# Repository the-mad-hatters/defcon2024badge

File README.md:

# defcon2024badge

See https://madhatters.lol for details

The Mad Hatter Auto Revelator badge and Madragrammaton SAO will be available at the Hacker Warehouse at DC32.

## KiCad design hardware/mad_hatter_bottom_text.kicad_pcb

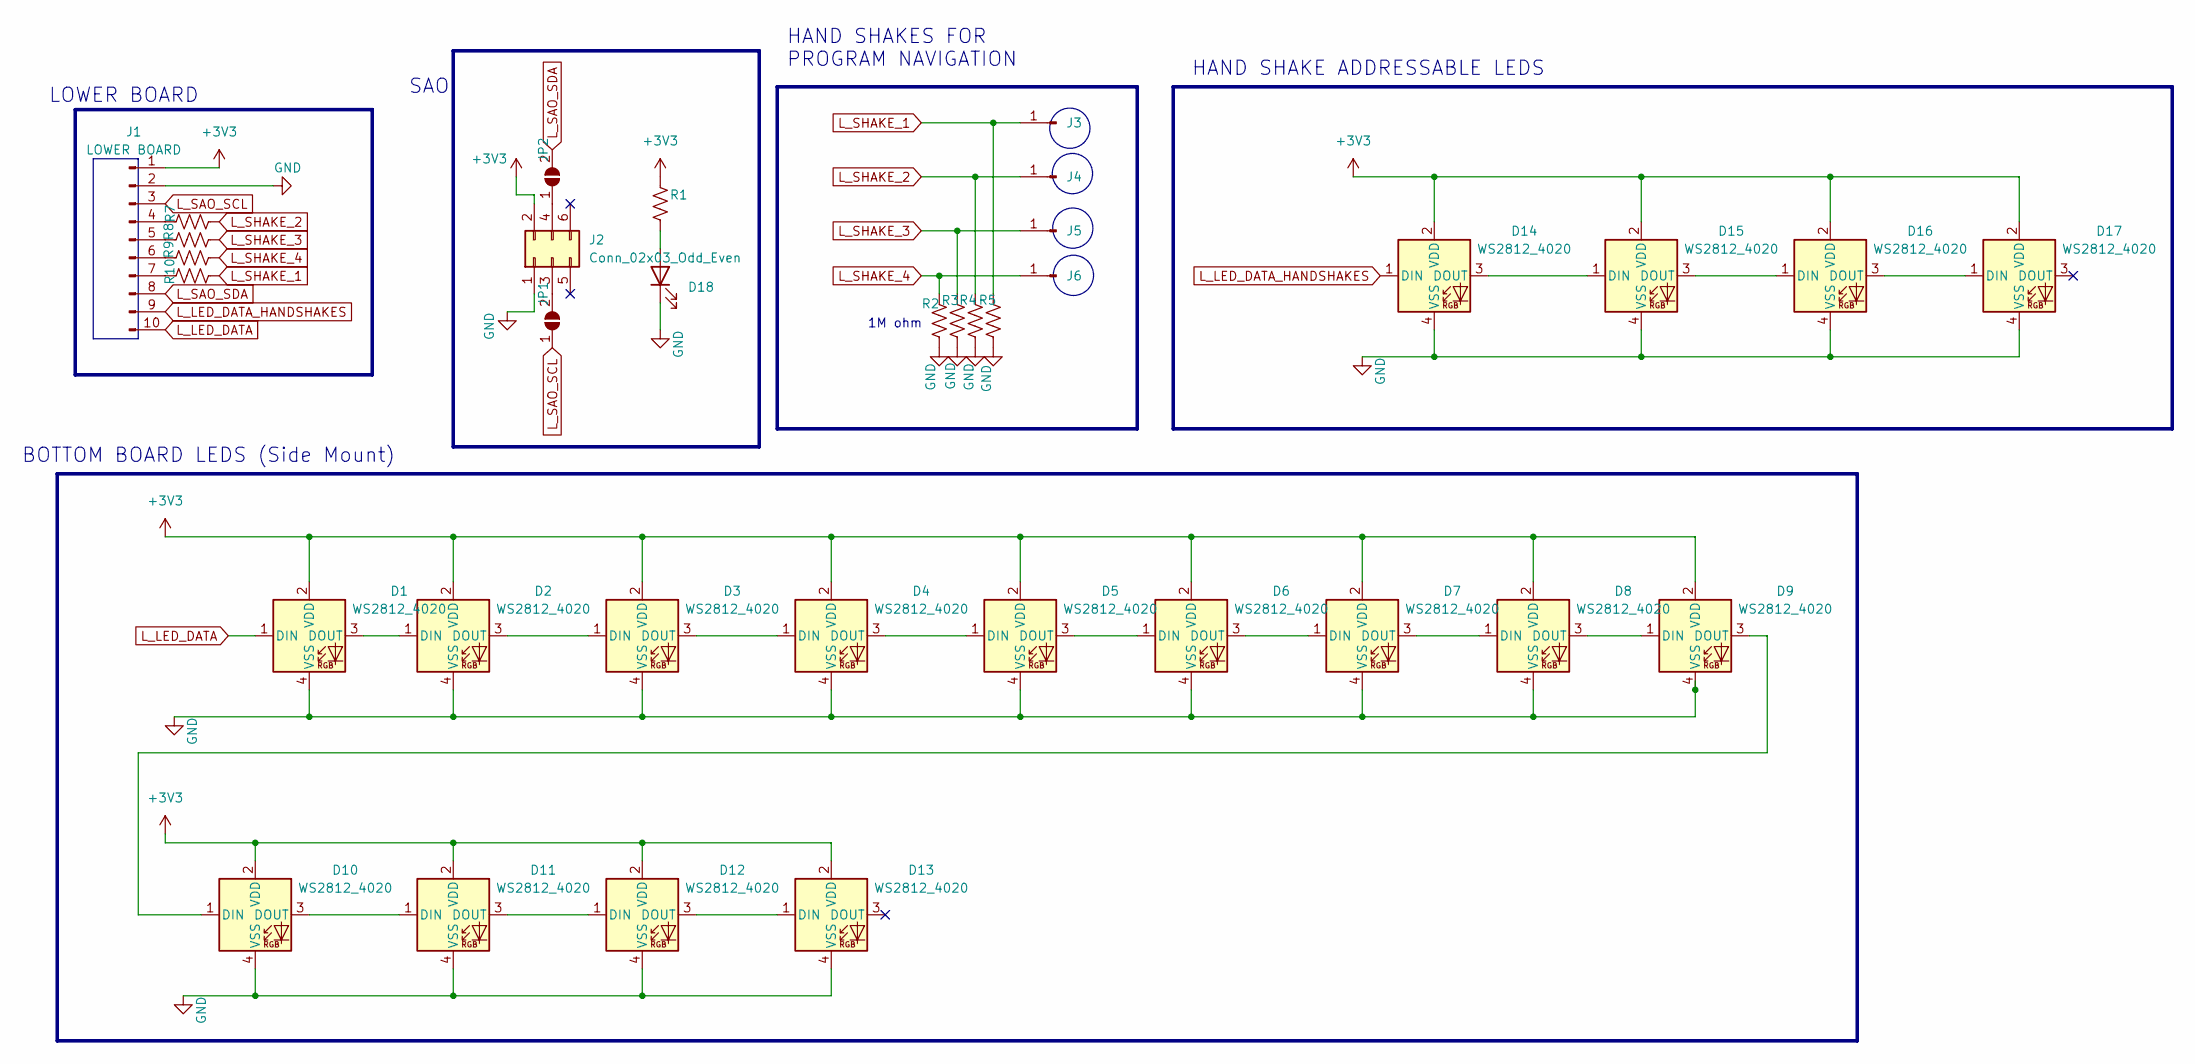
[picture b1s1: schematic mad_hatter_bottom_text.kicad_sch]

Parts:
D1, D2, D3, D4, D5, D6, D7, D8, D9, D10, D11, D12, D13, D14, D15, D16, D17: WS2812_4020; sk6812-side-a
D18: LED; LED_1206_3216Metric_Pad1.42x1.75mm_HandSolder
J1: LOWER BOARD; mad_hatter_lower_board_connector
J2: Conn_02x03_Odd_Even; sao_footprint
J3, J4, J5, J6: Conn_01x01_Pin; mad_hatter_touch_button
JP1, JP2: SolderJumper_2_Open; SolderJumper-2_P1.3mm_Open_Pad1.0x1.5mm
R1, R2, R3, R4, R5, R7, R8, R9, R10: R_US; R_0603_1608Metric_Pad0.98x0.95mm_HandSolder

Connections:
+3V3: D1.2 (VDD), D2.2 (VDD), D3.2 (VDD), D4.2 (VDD), D5.2 (VDD), D6.2 (VDD), D7.2 (VDD), D8.2 (VDD), D9.2 (VDD), D10.2 (VDD), D11.2 (VDD), D12.2 (VDD), D13.2 (VDD), D14.2 (VDD), D15.2 (VDD), D16.2 (VDD), D17.2 (VDD), J1.1, J2.2, R1.1
GND: D1.4 (VSS), D2.4 (VSS), D3.4 (VSS), D4.4 (VSS), D5.4 (VSS), D6.4 (VSS), D7.4 (VSS), D8.4 (VSS), D9.4 (VSS), D10.4 (VSS), D11.4 (VSS), D12.4 (VSS), D13.4 (VSS), D14.4 (VSS), D15.4 (VSS), D16.4 (VSS), D17.4 (VSS), D18.1 (K), J1.2, J2.1, R2.2, R3.2, R4.2, R5.2
L_LED_DATA: D1.1 (DIN), J1.10
L_LED_DATA_HANDSHAKES: D14.1 (DIN), J1.9
L_SAO_SCL: J1.3, JP1.1 (A)
L_SAO_SDA: J1.8, JP2.2 (B)
L_SHAKE_1: J3.1, R5.1, R10.1
L_SHAKE_2: J4.1, R4.1, R7.1
L_SHAKE_3: J5.1, R3.1, R8.1
L_SHAKE_4: J6.1, R2.1, R9.1
unnamed: D1.3 (DOUT), D2.1 (DIN)
unnamed: D2.3 (DOUT), D3.1 (DIN)
unnamed: D3.3 (DOUT), D4.1 (DIN)
unnamed: D4.3 (DOUT), D5.1 (DIN)
unnamed: D5.3 (DOUT), D6.1 (DIN)
unnamed: D6.3 (DOUT), D7.1 (DIN)
unnamed: D7.3 (DOUT), D8.1 (DIN)
unnamed: D8.3 (DOUT), D9.1 (DIN)
unnamed: D9.3 (DOUT), D10.1 (DIN)
unnamed: D10.3 (DOUT), D11.1 (DIN)
unnamed: D11.3 (DOUT), D12.1 (DIN)
unnamed: D12.3 (DOUT), D13.1 (DIN)
unnamed: D14.3 (DOUT), D15.1 (DIN)
unnamed: D15.3 (DOUT), D16.1 (DIN)
unnamed: D16.3 (DOUT), D17.1 (DIN)
unnamed: D18.2 (A), R1.2
unnamed: J1.4, R7.2
unnamed: J1.5, R8.2
unnamed: J1.6, R9.2
unnamed: J1.7, R10.2
unnamed: J2.3, JP1.2 (B)
unnamed: J2.4, JP2.1 (A)

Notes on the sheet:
HAND SHAKES FOR PROGRAM NAVIGATION
LOWER BOARD
SAO
HAND SHAKE ADDRESSABLE LEDS
BOTTOM BOARD LEDS (Side Mount)
1M ohm

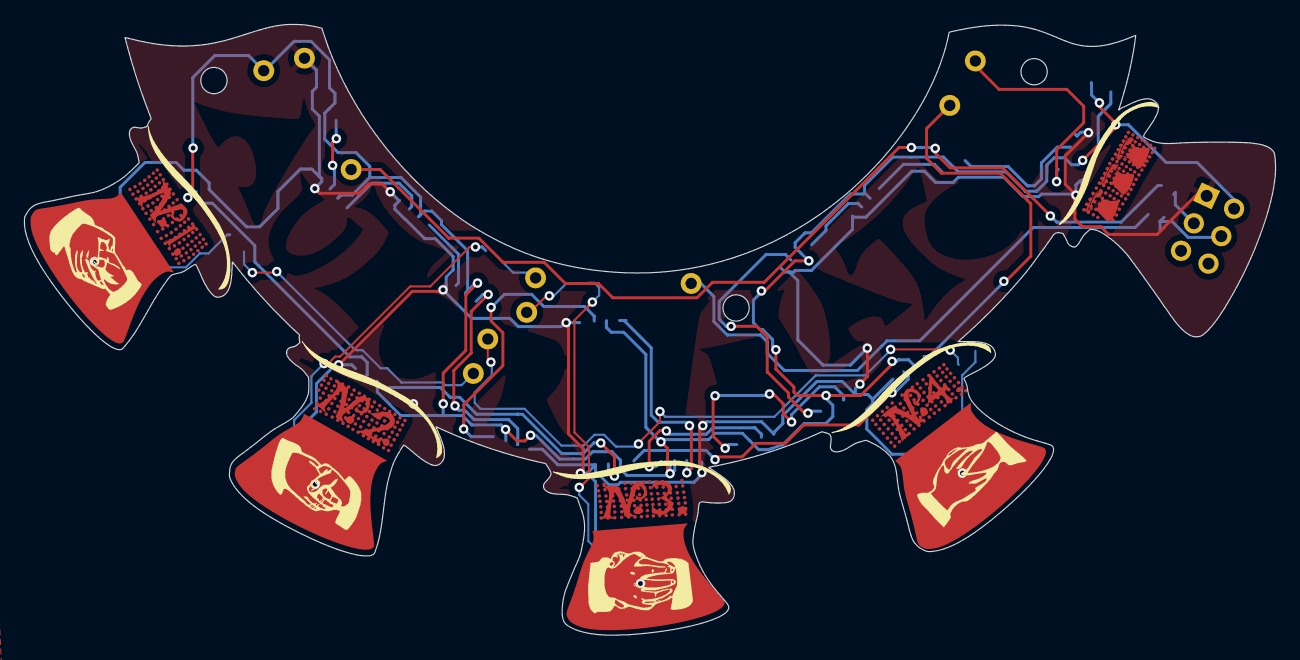
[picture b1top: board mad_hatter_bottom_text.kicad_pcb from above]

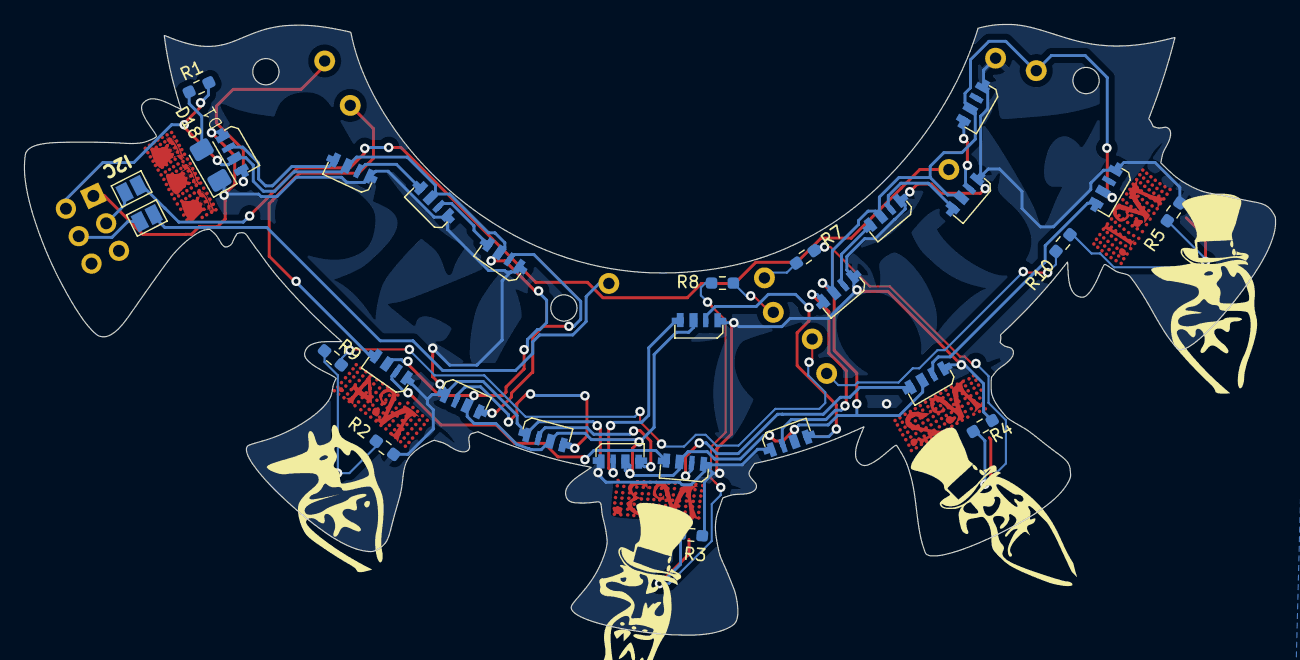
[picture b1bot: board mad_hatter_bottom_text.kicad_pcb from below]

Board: 2 copper layers, 104.9 x 51.2 mm, 35 parts (29 on the bottom side), 32 nets.

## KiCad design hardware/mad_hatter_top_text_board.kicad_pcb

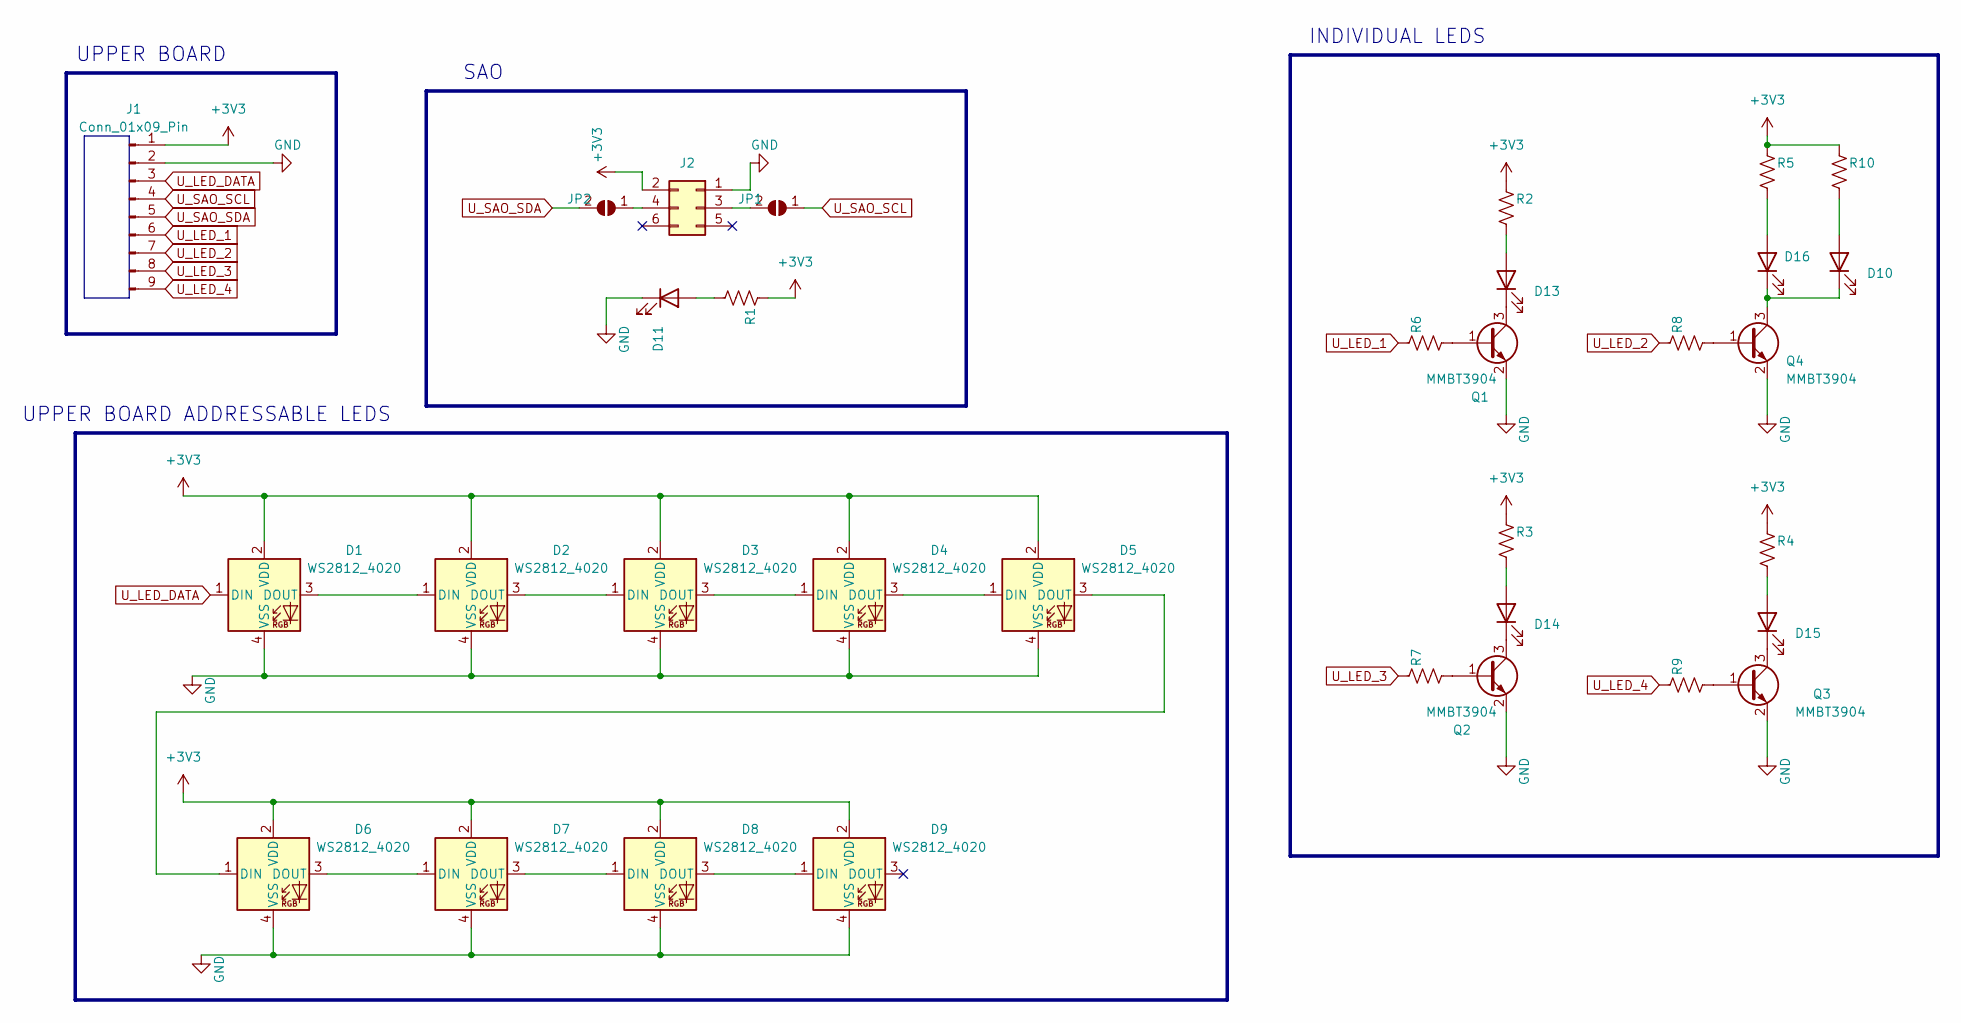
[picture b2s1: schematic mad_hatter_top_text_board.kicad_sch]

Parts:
D1, D2, D3, D4, D5, D6, D7, D8, D9: WS2812_4020; sk6812-side-a
D10: LED; LED_0805_2012Metric_Pad1.15x1.40mm_HandSolder
D11, D13, D14, D15, D16: LED; LED_1206_3216Metric_Pad1.42x1.75mm_HandSolder
J1: Conn_01x09_Pin; mad_hatter_upper_board_connector
J2: Conn_02x03_Odd_Even; sao_footprint
JP1, JP2: SolderJumper_2_Open; SolderJumper-2_P1.3mm_Open_Pad1.0x1.5mm
Q1, Q2, Q3, Q4: MMBT3904; SOT-23
R1, R2, R3, R4, R5, R6, R7, R8, R9, R10: R_US; R_0603_1608Metric_Pad0.98x0.95mm_HandSolder

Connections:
+3V3: D1.2 (VDD), D2.2 (VDD), D3.2 (VDD), D4.2 (VDD), D5.2 (VDD), D6.2 (VDD), D7.2 (VDD), D8.2 (VDD), D9.2 (VDD), J1.1, J2.2, R1.1, R2.1, R3.1, R4.1, R5.1, R10.1
GND: D1.4 (VSS), D2.4 (VSS), D3.4 (VSS), D4.4 (VSS), D5.4 (VSS), D6.4 (VSS), D7.4 (VSS), D8.4 (VSS), D9.4 (VSS), D11.1 (K), J1.2, J2.1, Q1.2 (E), Q2.2 (E), Q3.2 (E), Q4.2 (E)
unnamed: D1.3 (DOUT), D2.1 (DIN)
unnamed: D2.3 (DOUT), D3.1 (DIN)
unnamed: D3.3 (DOUT), D4.1 (DIN)
unnamed: D4.3 (DOUT), D5.1 (DIN)
unnamed: D5.3 (DOUT), D6.1 (DIN)
unnamed: D6.3 (DOUT), D7.1 (DIN)
unnamed: D7.3 (DOUT), D8.1 (DIN)
unnamed: D8.3 (DOUT), D9.1 (DIN)
unnamed: D10.2 (A), R10.2
unnamed: D10.1 (K), D16.1 (K), Q4.3 (C)
unnamed: D11.2 (A), R1.2
unnamed: D13.2 (A), R2.2
unnamed: D13.1 (K), Q1.3 (C)
unnamed: D14.2 (A), R3.2
unnamed: D14.1 (K), Q2.3 (C)
unnamed: D15.2 (A), R4.2
unnamed: D15.1 (K), Q3.3 (C)
unnamed: D16.2 (A), R5.2
unnamed: J2.3, JP1.2 (B)
unnamed: J2.4, JP2.1 (A)
unnamed: Q1.1 (B), R6.2
unnamed: Q2.1 (B), R7.2
unnamed: Q3.1 (B), R9.2
unnamed: Q4.1 (B), R8.2
U_LED_1: J1.6, R6.1
U_LED_2: J1.7, R8.1
U_LED_3: J1.8, R7.1
U_LED_4: J1.9, R9.1
U_LED_DATA: D1.1 (DIN), J1.3
U_SAO_SCL: J1.4, JP1.1 (A)
U_SAO_SDA: J1.5, JP2.2 (B)

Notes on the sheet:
UPPER BOARD
INDIVIDUAL LEDS
UPPER BOARD ADDRESSABLE LEDS
SAO

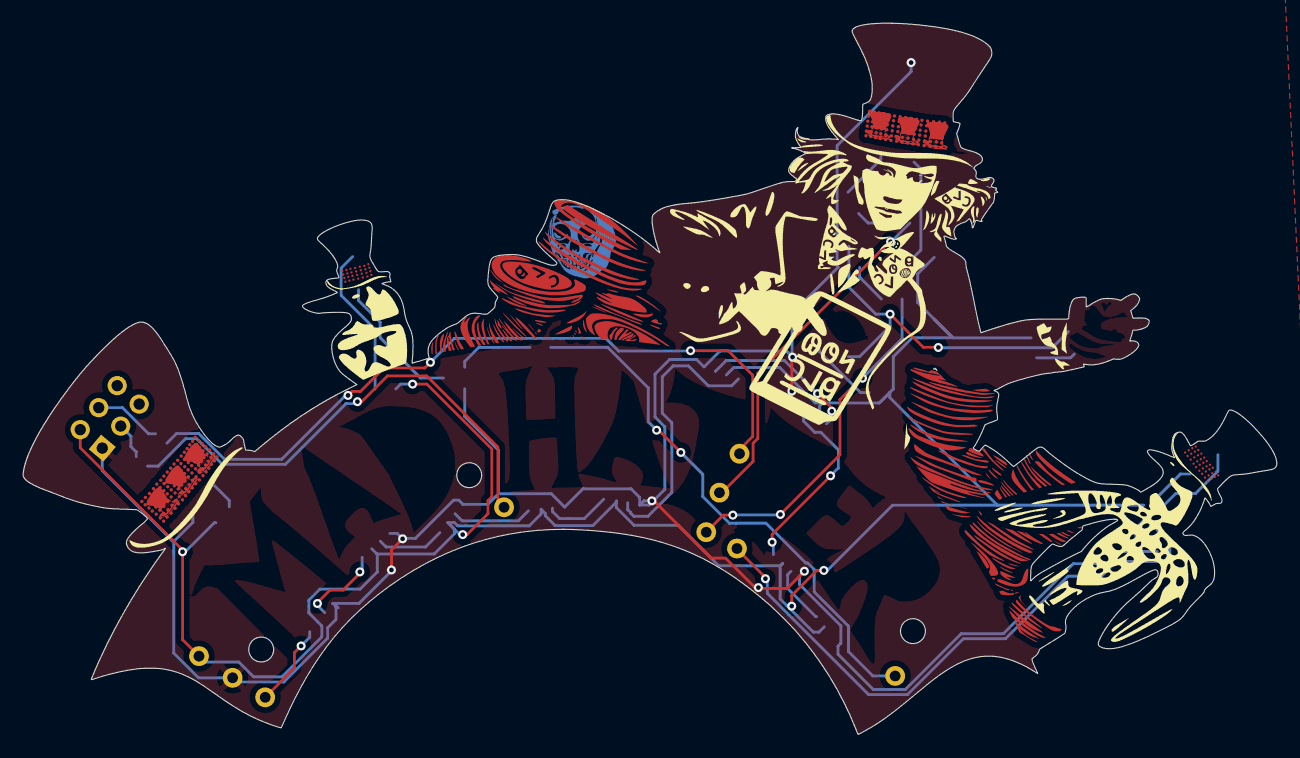
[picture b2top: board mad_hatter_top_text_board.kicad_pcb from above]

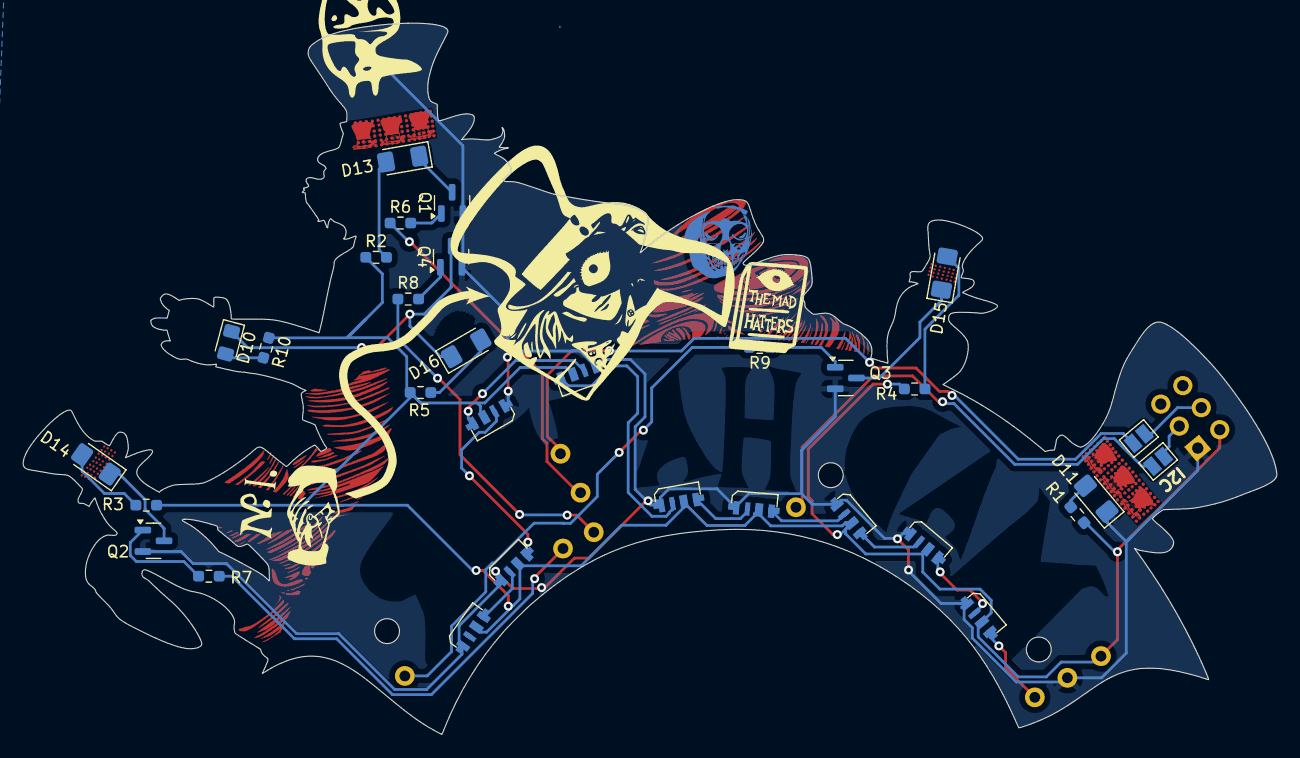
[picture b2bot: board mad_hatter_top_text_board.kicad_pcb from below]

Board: 2 copper layers, 110.8 x 62.9 mm, 33 parts (31 on the bottom side), 33 nets.

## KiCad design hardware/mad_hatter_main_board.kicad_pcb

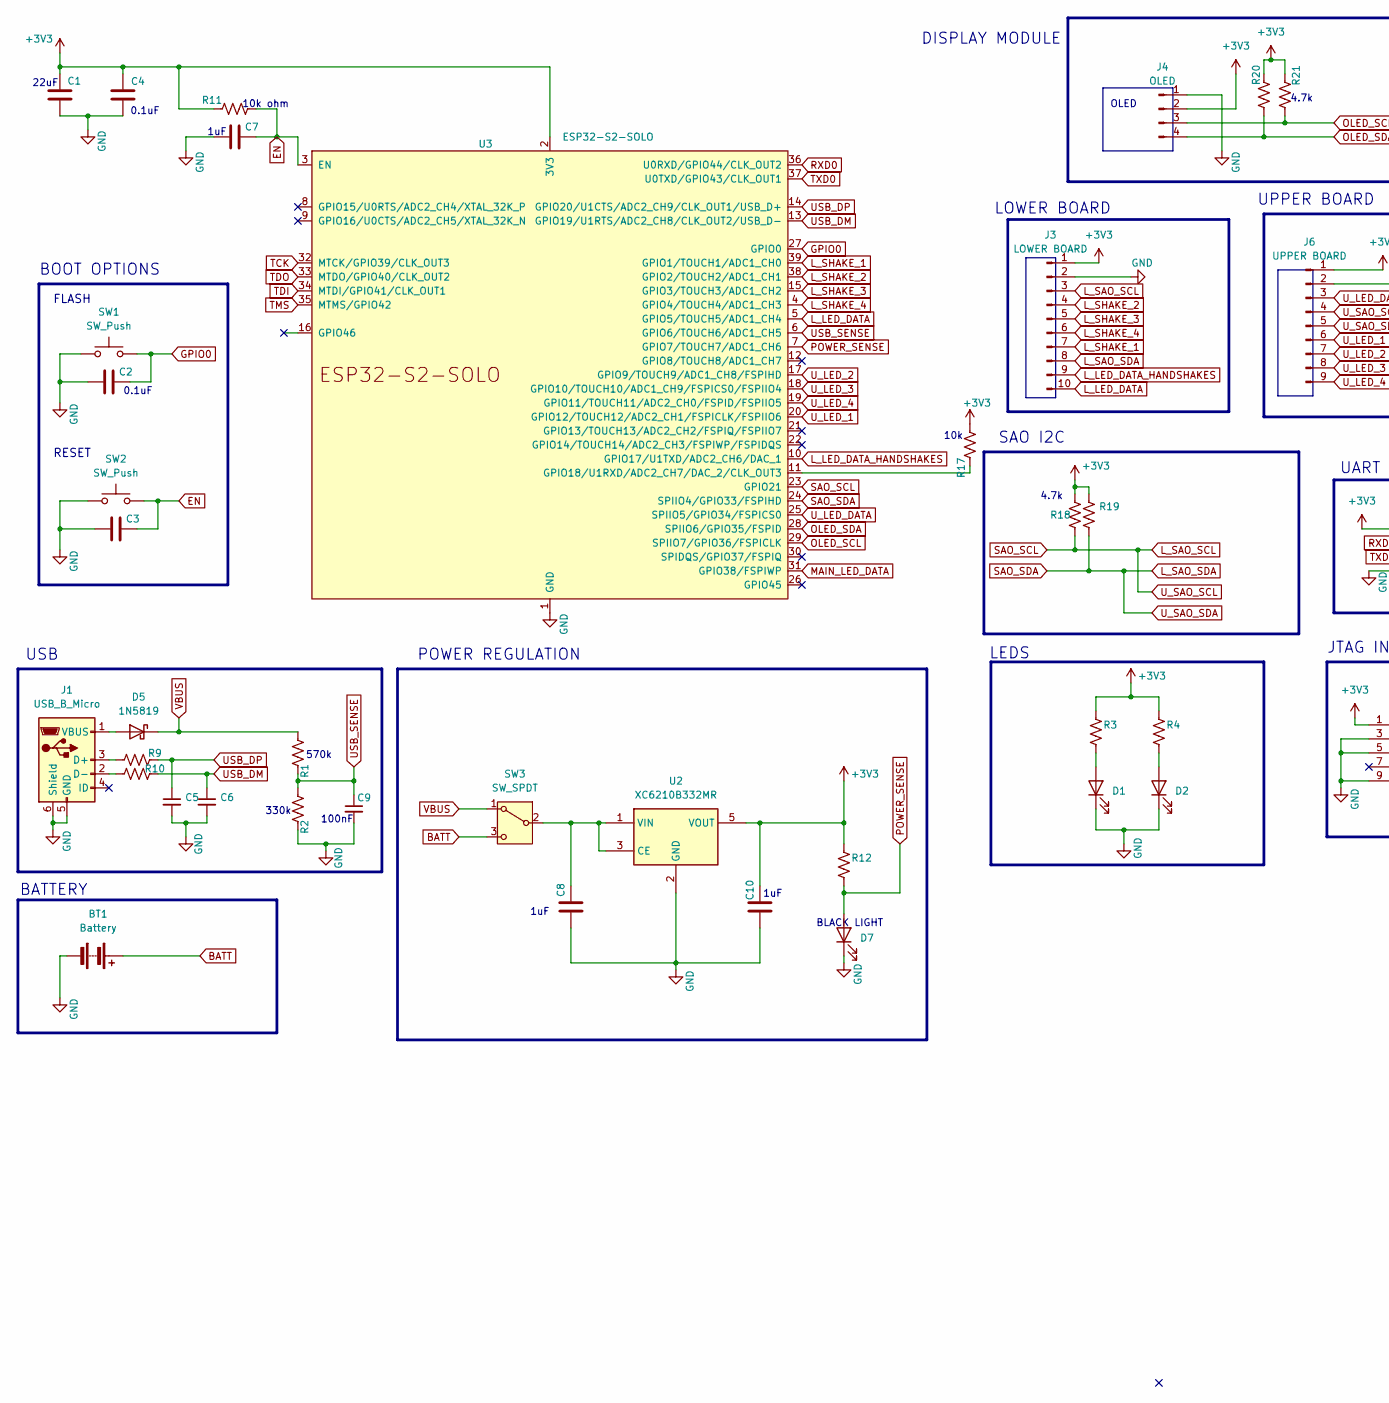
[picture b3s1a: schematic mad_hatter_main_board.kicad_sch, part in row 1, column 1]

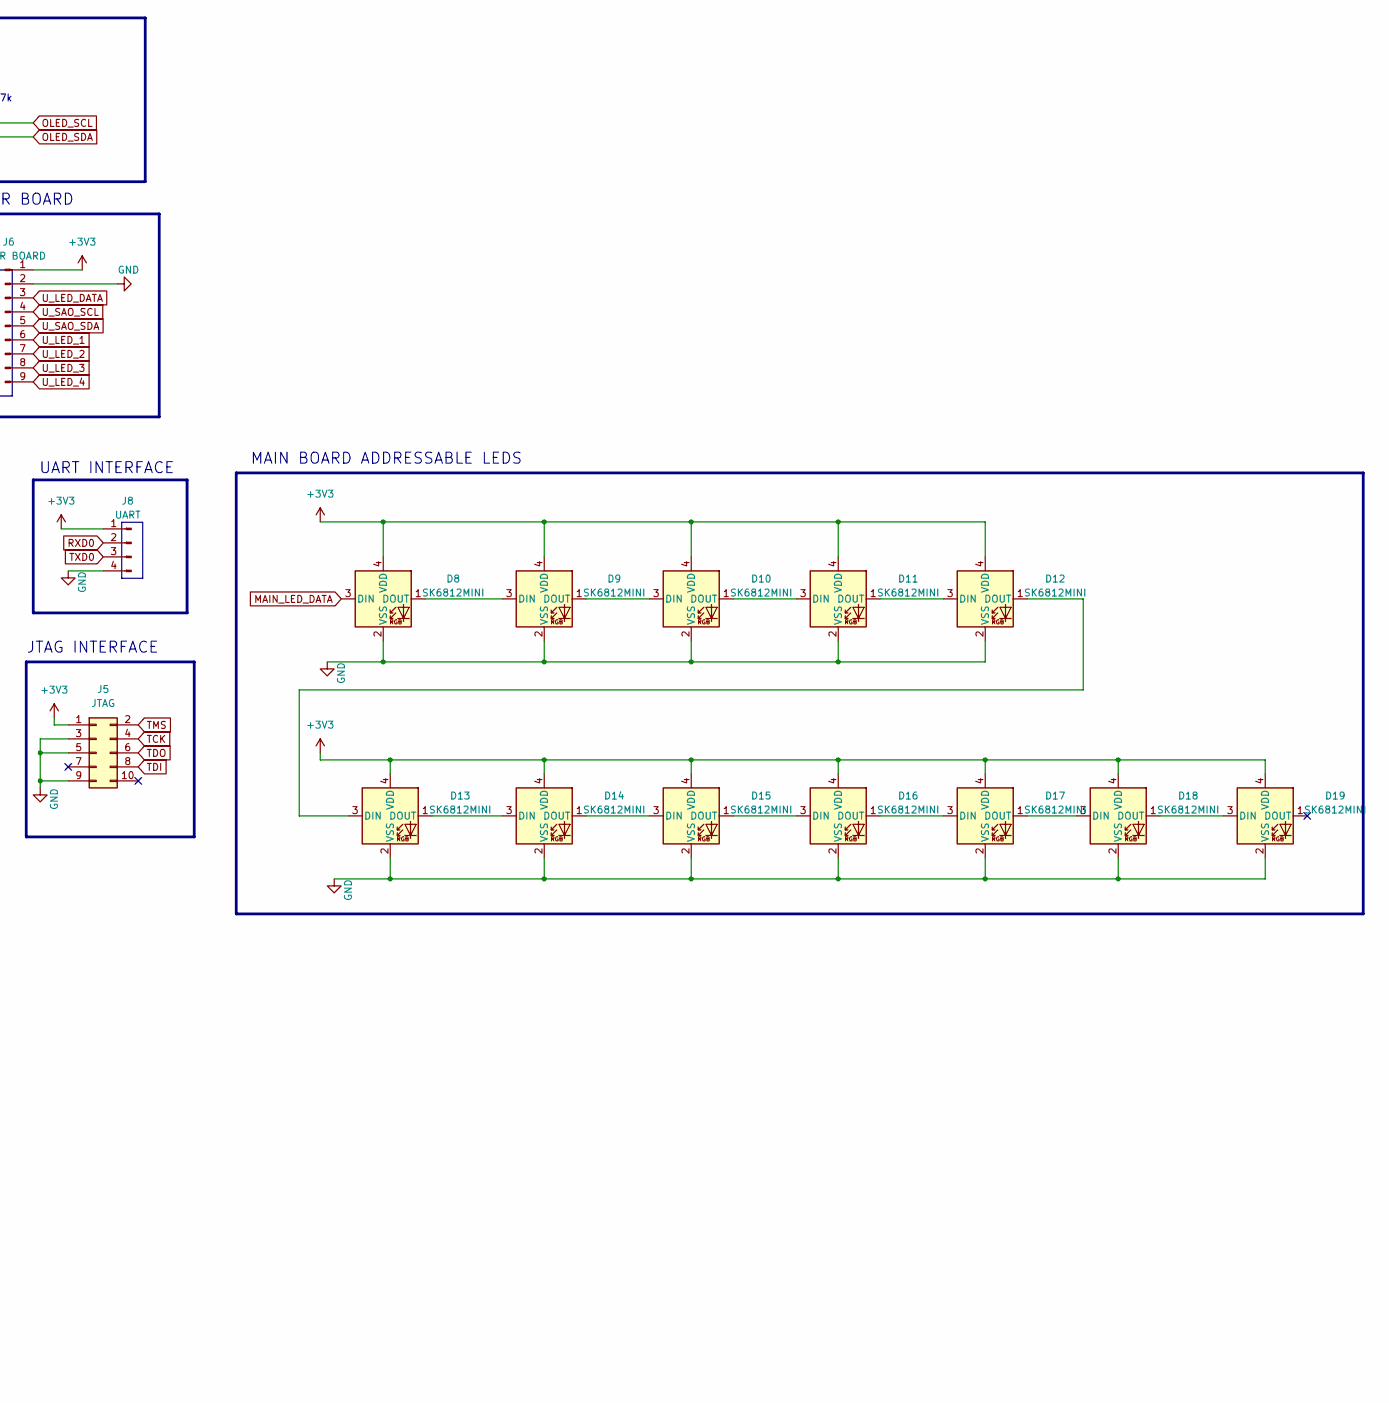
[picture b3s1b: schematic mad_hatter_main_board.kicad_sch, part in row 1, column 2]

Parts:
BT1: Battery; mad_hatter_3_AA_battery
C1: C; C_0805_2012Metric_Pad1.18x1.45mm_HandSolder
C2, C3, C4, C7, C8, C10: C; C_0603_1608Metric_Pad1.08x0.95mm_HandSolder
C5, C6, C9: 10uF; C_0603_1608Metric_Pad1.08x0.95mm_HandSolder
D1, D2, D7: LED; LED_1206_3216Metric_Pad1.42x1.75mm_HandSolder
D5: 1N5819; D_DO-41_SOD81_P10.16mm_Horizontal
D8, D9, D10, D11, D12, D13, D14, D15, D16, D17, D18, D19: SK6812MINI; mad_hatter_sk6812mini
J1: USB_B_Micro; USB_Micro-B_Amphenol_10118193-0001LF_Horizontal
J3: LOWER BOARD; mad_hatter_lower_board_connector
J4: OLED; oled_display
J5: JTAG; mad_hatter_jtag_sneaky_connector
J6: UPPER BOARD; mad_hatter_upper_board_connector
J8: UART; mad_hatter_sneaky_uart_connector
R1, R2, R3, R4, R9, R10, R11, R12, R17, R18, R19, R20, R21: R_US; R_0603_1608Metric_Pad0.98x0.95mm_HandSolder
SW1, SW2: SW_Push; SW_SPST_TL3305A
SW3: SW_SPDT; mad_hatter_switch_2
U2: XC6210B332MR; SOT-23-5
U3: ESP32-S2-SOLO

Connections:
+3V3: C1.1, C4.1, C10.1, D8.4 (VDD), D9.4 (VDD), D10.4 (VDD), D11.4 (VDD), D12.4 (VDD), D13.4 (VDD), D14.4 (VDD), D15.4 (VDD), D16.4 (VDD), D17.4 (VDD), D18.4 (VDD), D19.4 (VDD), J3.1, J4.2, J5.1, J6.1, J8.1, R3.1, R4.1, R11.2, R12.1, R17.1, R18.1, R19.1, R20.2, R21.2, U2.5 (VOUT), U3.2 (3V3)
BATT: BT1.1 (+), SW3.3 (C)
EN: C3.1, C7.1, R11.1, SW2.2, U3.3 (EN)
GND: BT1.2 (-), C1.2, C2.2, C3.2, C4.2, C5.2, C6.2, C7.2, C8.2, C9.2, C10.2, D1.1 (K), D2.1 (K), D7.1 (K), D8.2 (VSS), D9.2 (VSS), D10.2 (VSS), D11.2 (VSS), D12.2 (VSS), D13.2 (VSS), D14.2 (VSS), D15.2 (VSS), D16.2 (VSS), D17.2 (VSS), D18.2 (VSS), D19.2 (VSS), J1.5 (GND), J1.6 (Shield), J3.2, J4.1, J5.3, J5.5, J5.9, J6.2, J8.4, R2.1, SW1.1, SW2.1, U2.2 (GND), U3.1 (GND), U3.40 (GND), U3.41 (GND)
GPIO0: C2.1, SW1.2, U3.27 (GPIO0)
L_LED_DATA: J3.10, U3.5 (GPIO5/TOUCH5/ADC1_CH4)
L_LED_DATA_HANDSHAKES: J3.9, U3.10 (GPIO17/U1TXD/ADC2_CH6/DAC_1)
L_SAO_SCL: J3.3, J6.4, R18.2, U3.23 (GPIO21)
L_SAO_SDA: J3.8, J6.5, R19.2, U3.24 (SPIIO4/GPIO33/FSPIHD)
L_SHAKE_1: J3.7, U3.39 (GPIO1/TOUCH1/ADC1_CH0)
L_SHAKE_2: J3.4, U3.38 (GPIO2/TOUCH2/ADC1_CH1)
L_SHAKE_3: J3.5, U3.15 (GPIO3/TOUCH3/ADC1_CH2)
L_SHAKE_4: J3.6, U3.4 (GPIO4/TOUCH4/ADC1_CH3)
MAIN_LED_DATA: D8.3 (DIN), U3.31 (GPIO38/FSPIWP)
unnamed: D1.2 (A), R3.2
unnamed: D2.2 (A), R4.2
unnamed: D5.2 (A), J1.1 (VBUS)
unnamed: D8.1 (DOUT), D9.3 (DIN)
unnamed: D9.1 (DOUT), D10.3 (DIN)
unnamed: D10.1 (DOUT), D11.3 (DIN)
unnamed: D11.1 (DOUT), D12.3 (DIN)
unnamed: D12.1 (DOUT), D13.3 (DIN)
unnamed: D13.1 (DOUT), D14.3 (DIN)
unnamed: D14.1 (DOUT), D15.3 (DIN)
unnamed: D15.1 (DOUT), D16.3 (DIN)
unnamed: D16.1 (DOUT), D17.3 (DIN)
unnamed: D17.1 (DOUT), D18.3 (DIN)
unnamed: D18.1 (DOUT), D19.3 (DIN)
unnamed: J1.3 (D+), R9.2
unnamed: J1.2 (D-), R10.2
unnamed: C8.1, SW3.2 (B), U2.1 (VIN), U2.3 (CE)
unnamed: R17.2, U3.11 (GPIO18/U1RXD/ADC2_CH7/DAC_2/CLK_OUT3)
OLED_SCL: J4.3, R21.1, U3.29 (SPIIO7/GPIO36/FSPICLK)
OLED_SDA: J4.4, R20.1, U3.28 (SPIIO6/GPIO35/FSPID)
POWER_SENSE: D7.2 (A), R12.2, U3.7 (GPIO7/TOUCH7/ADC1_CH6)
RXD0: J8.2, U3.36 (U0RXD/GPIO44/CLK_OUT2)
TCK: J5.4, U3.32 (MTCK/GPIO39/CLK_OUT3)
TDI: J5.8, U3.34 (MTDI/GPIO41/CLK_OUT1)
TDO: J5.6, U3.33 (MTDO/GPIO40/CLK_OUT2)
TMS: J5.2, U3.35 (MTMS/GPIO42)
TXD0: J8.3, U3.37 (U0TXD/GPIO43/CLK_OUT1)
USB_DM: C6.1, R10.1, U3.13 (GPIO19/U1RTS/ADC2_CH8/CLK_OUT2/USB_D-)
USB_DP: C5.1, R9.1, U3.14 (GPIO20/U1CTS/ADC2_CH9/CLK_OUT1/USB_D+)
USB_SENSE: C9.1, R1.1, R2.2, U3.6 (GPIO6/TOUCH6/ADC1_CH5)
U_LED_1: J6.6, U3.20 (GPIO12/TOUCH12/ADC2_CH1/FSPICLK/FSPIIO6)
U_LED_2: J6.7, U3.17 (GPIO9/TOUCH9/ADC1_CH8/FSPIHD)
U_LED_3: J6.8, U3.18 (GPIO10/TOUCH10/ADC1_CH9/FSPICS0/FSPIIO4)
U_LED_4: J6.9, U3.19 (GPIO11/TOUCH11/ADC2_CH0/FSPID/FSPIIO5)
U_LED_DATA: J6.3, U3.25 (SPIIO5/GPIO34/FSPICS0)
VBUS: D5.1 (K), R1.2, SW3.1 (A)

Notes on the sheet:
0.1uF
LEDS
BOOT OPTIONS
BATTERY
SAO I2C
UART INTERFACE
JTAG INTERFACE
10k ohm
POWER REGULATION
22uF
OLED
RESET
330k
MAIN BOARD ADDRESSABLE LEDS
4.7k
1uF
USB
570k
FLASH
100nF
10k
UPPER BOARD
DISPLAY MODULE
BLACK LIGHT
LOWER BOARD

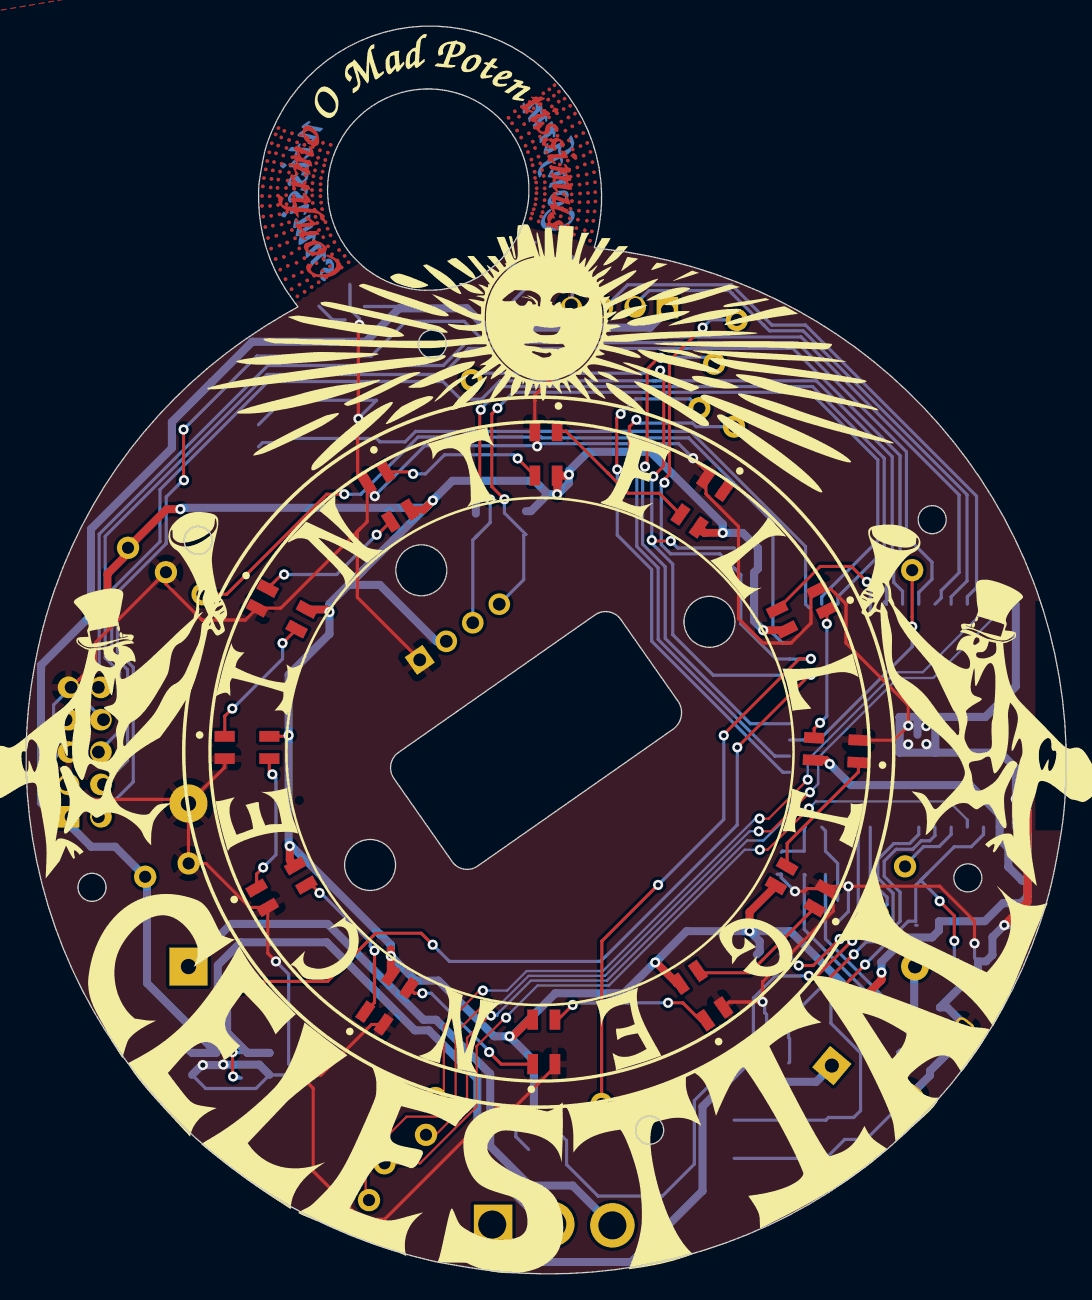
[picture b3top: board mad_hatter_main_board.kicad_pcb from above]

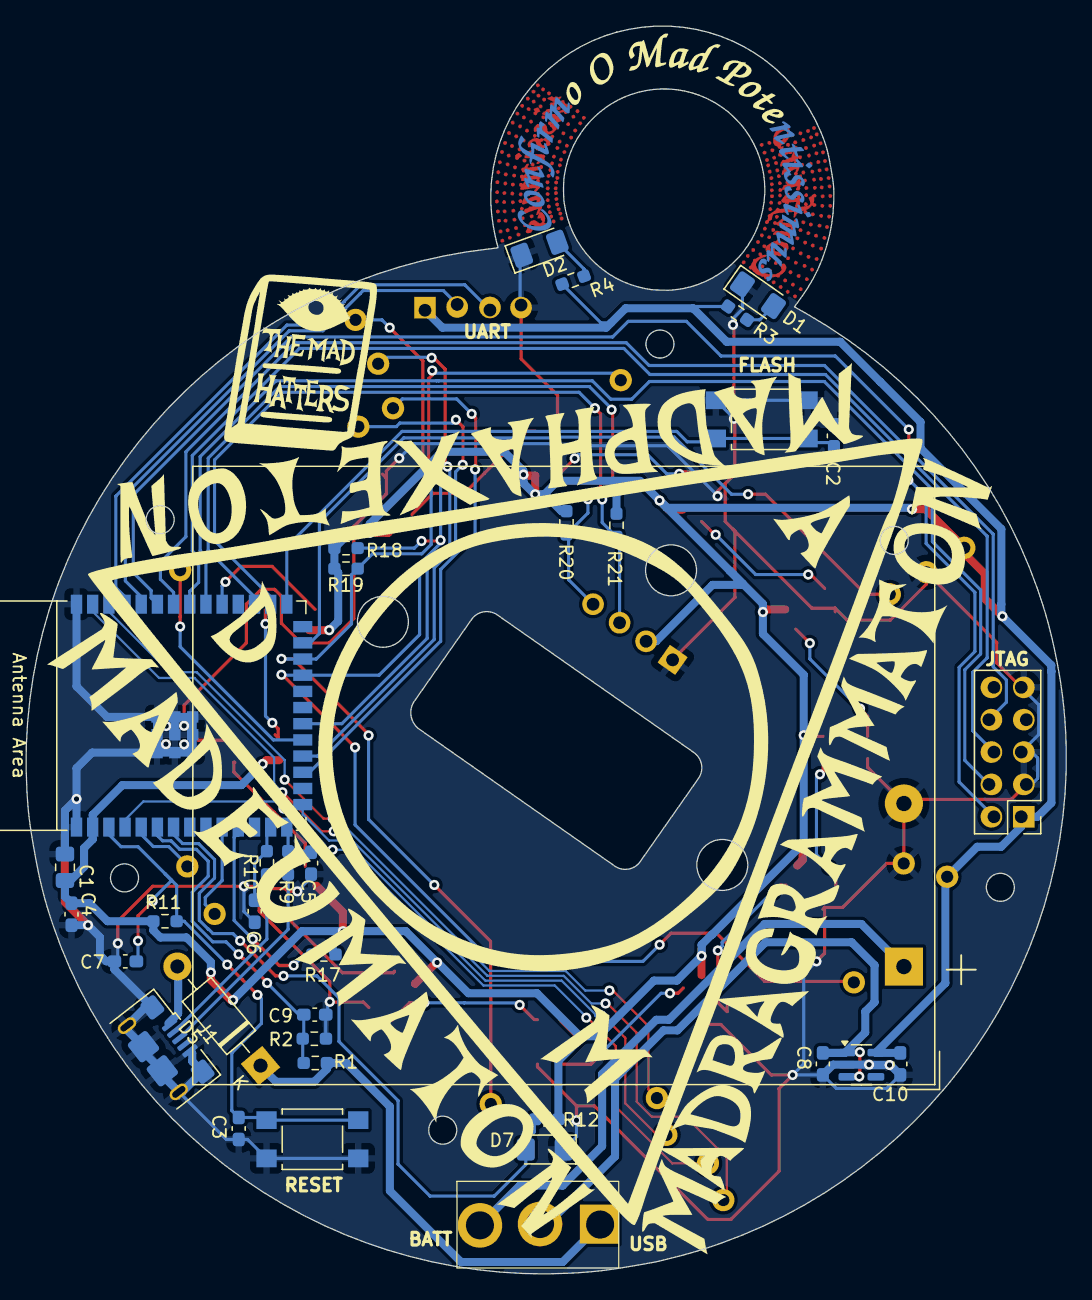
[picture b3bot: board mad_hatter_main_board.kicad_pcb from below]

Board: 2 copper layers, 81.6 x 97.9 mm, 51 parts (35 on the bottom side), 50 nets.

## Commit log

2024-06-25 Working code for some of the functionality
    I don't have everything ported over quite yet due to messing around with
    too many other aspects of this but the code here at least works and
    doesn't _appear_ to have any random panics, etc. so I might as well get
    this up so others can see it. I'll have a lot more incoming both to
    match existing functionality in the original arduino code as well as to
    improve things further.
2024-06-25 A little cleanup and change to title
    In order to more closely reach parity with the original design I changed
    it to draw static centered text on the display instead of scrolling the
    text across the screen. Either way works fine.
2024-06-27 Create hardware
2024-06-27 Create main_board
2024-06-27 Lots more misc. changes
    Sorry, sparse commit message... can't be bothered to enumerate the
    changes right now
2024-06-27 Add brightness control for main LED ring
2024-06-29 Some more helpers in the display manager
    I figured it would be useful to be able to prompt a user with some
    options so I made a method to be able to render a prompt with some
    options and then since I saw that the v5 Arduino code has text input for
    the user's handle I figured I'd implement something that can do that...
    I actually didn't look closely at what it looks like in the sketch and
    instead just implemented my own concept for how to do text entry. We can
2024-06-29 Refactored code for scenes
    Starting to incorporate the color palettes as in the v5 sketch.
    Abstracted a couple helper methods into `SceneBase`
2024-06-30 Update truths.txt
    added truths
2024-06-30 Update revelations.txt
    removed magic 8 ball responses.. added more revelations
2024-06-30 Update truths_nsfw.txt
    more nsfw truths
2024-06-30 Update revelations_nsfw.txt
    removed magic 8 ball responses.. added some nsfw revelations
2024-06-30 Update emeter.txt
    adding emeter text
2024-07-02 Lots of changes relating to display components
    Instead of just having other code have to handle all of the state for
    some of the UI features/components I turned them into managed features.
    This makes it way easier and cleaner to work with.
2024-07-03 Refactored the scene handling code
    The LED scene code is no longer built such that you have to implement a
    separate class... it now just uses configuration defined for each scene
    and abstracts the rest. Also, I don't know why yet but some of the
    component handling stuff is no longer working... I'll debug that
2024-07-03 Put the rest of the scene definitions in
    Now the scenes are all here... can be tweaked as needed
2024-07-04 Touch input fixes and component refinements
    I figured out the dumb issue I caused with touch inputs not working
    right and fixed it... also made it less error prone for future
    modifications by using maps to keep track of input pins, LEDs, and
    associated 0-offset indices
2024-07-04 Major Home mode refactor to do menus better
    I redid a ton of the Home mode to implement submenu support and make it
    look cleaner. You can now select LED modes as well by navigating through
    them and selecting what you want to change it to.
    Navigation is:
    - Handshake 1: enter/exit (brings up the menu in Home mode)
    - Handshake 2: up/left
2024-07-04 Update ScenePalettes.h
    updated colors in scene palettes and added the rest of the main palettes
2024-07-04 Update SceneManager.h
    added American Jesus led mode
2024-07-04 Update SceneManager.cpp
    added American Jesus led mode
2024-07-04 Update Home.hpp
    add american jesus led mode to menu
2024-07-04 Update ScenePalettes.h
    added gone clear led palettes
2024-07-04 Update SceneManager.h
    add gone clear led mode
2024-07-04 Update SceneManager.cpp
    add gone clear led mode
2024-07-04 Update Home.hpp
    add gone clear led mode to menu
2024-07-05 Cleanup and small bugfix
    I accidentally was saving menuIndex in the Home mode when the user
    canceled/exited the menu which was setting it to -1. This made the list
    component unhappy and it didn't want to render... maybe that's another
    bug I should fix
2024-07-05 Lots of changes/fixes + new modes added
    Added the revelation, and magic 8 ball modes as well as fixing a number
    of things... particularly around scrolling text and random deadlocks
    that would happen due to FastLED
2024-07-05 Missed a change while resolving merge conflict in last commit
2024-07-05 Update ScenePalettes.h
    fine tune palettes.. hopefully better battery life
2024-07-05 Update SceneManager.cpp
    adjust led timing
2024-07-05 Update config.h
    adjust led brightness..
2024-07-05 more led modes, change to stay in led menu while selecting modes
2024-07-06 Switched to levels of Hell
2024-07-06 Lots more changes + Mad Hatter mode
    The Mad Hatter mode still has some bugs to work out but I should get
    sleep. Here's the latest code I have with tons of changes.
2024-07-06 Finished getting Mad Hatter Meter working
    A fair number of changes to fix the mode and hopefully have everything
    working now
2024-07-06 Added about mode
    Super simple about mode for showing an About screen with a link to the
    site. Also cleaned up some inconsistencies in the header files
2024-07-07 Build/flash docs and one code change
    Changed the mad hatter mode so that hitting handshake 1 just exits back
    to Home mode. Maybe we should do that with other modes too instead of
    having to do the long press to force them to exit. For now I just have
    the behavior for mad hatter now and for the about screen.
    Added docs explaining how to package up firmware binaries and how to
    flash them without needing to install things like PlatformIO. I also am
2024-07-09 Several changes
    - Changed the NSFW mode to be a global thing rather than a per-mode
    thing. Once you set it from anywhere it is set to the selected state
    for any mode
    - Made the repeat rate for when you press and hold an input shorter so
    that you can scroll more quickly through things
2024-07-09 Misc. stuff
    - Get the version from a version.h header
    - Bug fixes
2024-07-09 Added option to use password for NSFW prompt
    I defaulted it to use the password option for now but it's easily
    selectable by changing the #define for `NSFW_PROMPT_TYPE` in
    BadgeMode.h if you want to switch back to the activate/deactivate prompt
    I'm versioning this as 1.3.0 and including new firmware images in the
    builds/ directory
2024-07-09 Increase handle scroll speed
    Also bumped version for the release to v1.3.1
2024-07-10 Update truths_nsfw.txt
    removed blank line
2024-07-10 Create LICENSE
2024-07-10 Add offsets for UI rendering
    We needed a way to add at least a Y offset because the displays we have
    aren't aligned super well to the PCB cutout. This adds that support and
    sets a 4px Y offset so that things _look_ vertically centered.
    While I was in there I also implemented a feature I had forgotten about
    with the text entry component to make the cursor remain on screen when
    the text is too long for the screen width (ie. render the entered text
2024-08-06 Update truths.txt
    add truth
2024-08-06 Small spelling fix for one of the revelations
2024-08-06 Bump firmware version to 1.3.3
    Release message changes
